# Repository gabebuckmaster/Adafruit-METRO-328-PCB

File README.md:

# Stanford-EE-Metro-Mini

Microchip/Atmel generously donated ATMega328 chips for use in Stanford Electrical Engineering courses. This fork of the Adafruit Metro (Mini) repository contains the design files for our build of the Metro Mini using these donated components.

##*PCB files for the Adafruit METRO 328*

*Format is EagleCAD schematic and board layout*

*For more details, check out the product page at*

  * https://www.adafruit.com/products/2466

*Adafruit invests time and resources providing this open source design, please support Adafruit and open-source hardware by purchasing products from Adafruit!*

*Designed by Adafruit Industries.*

*Creative Commons Attribution, Share-Alike license, check license.txt for more information. Derivative of "Arduino UNO R3 Reference design" (http://www.arduino.cc/en/Main/ArduinoBoardUno)*

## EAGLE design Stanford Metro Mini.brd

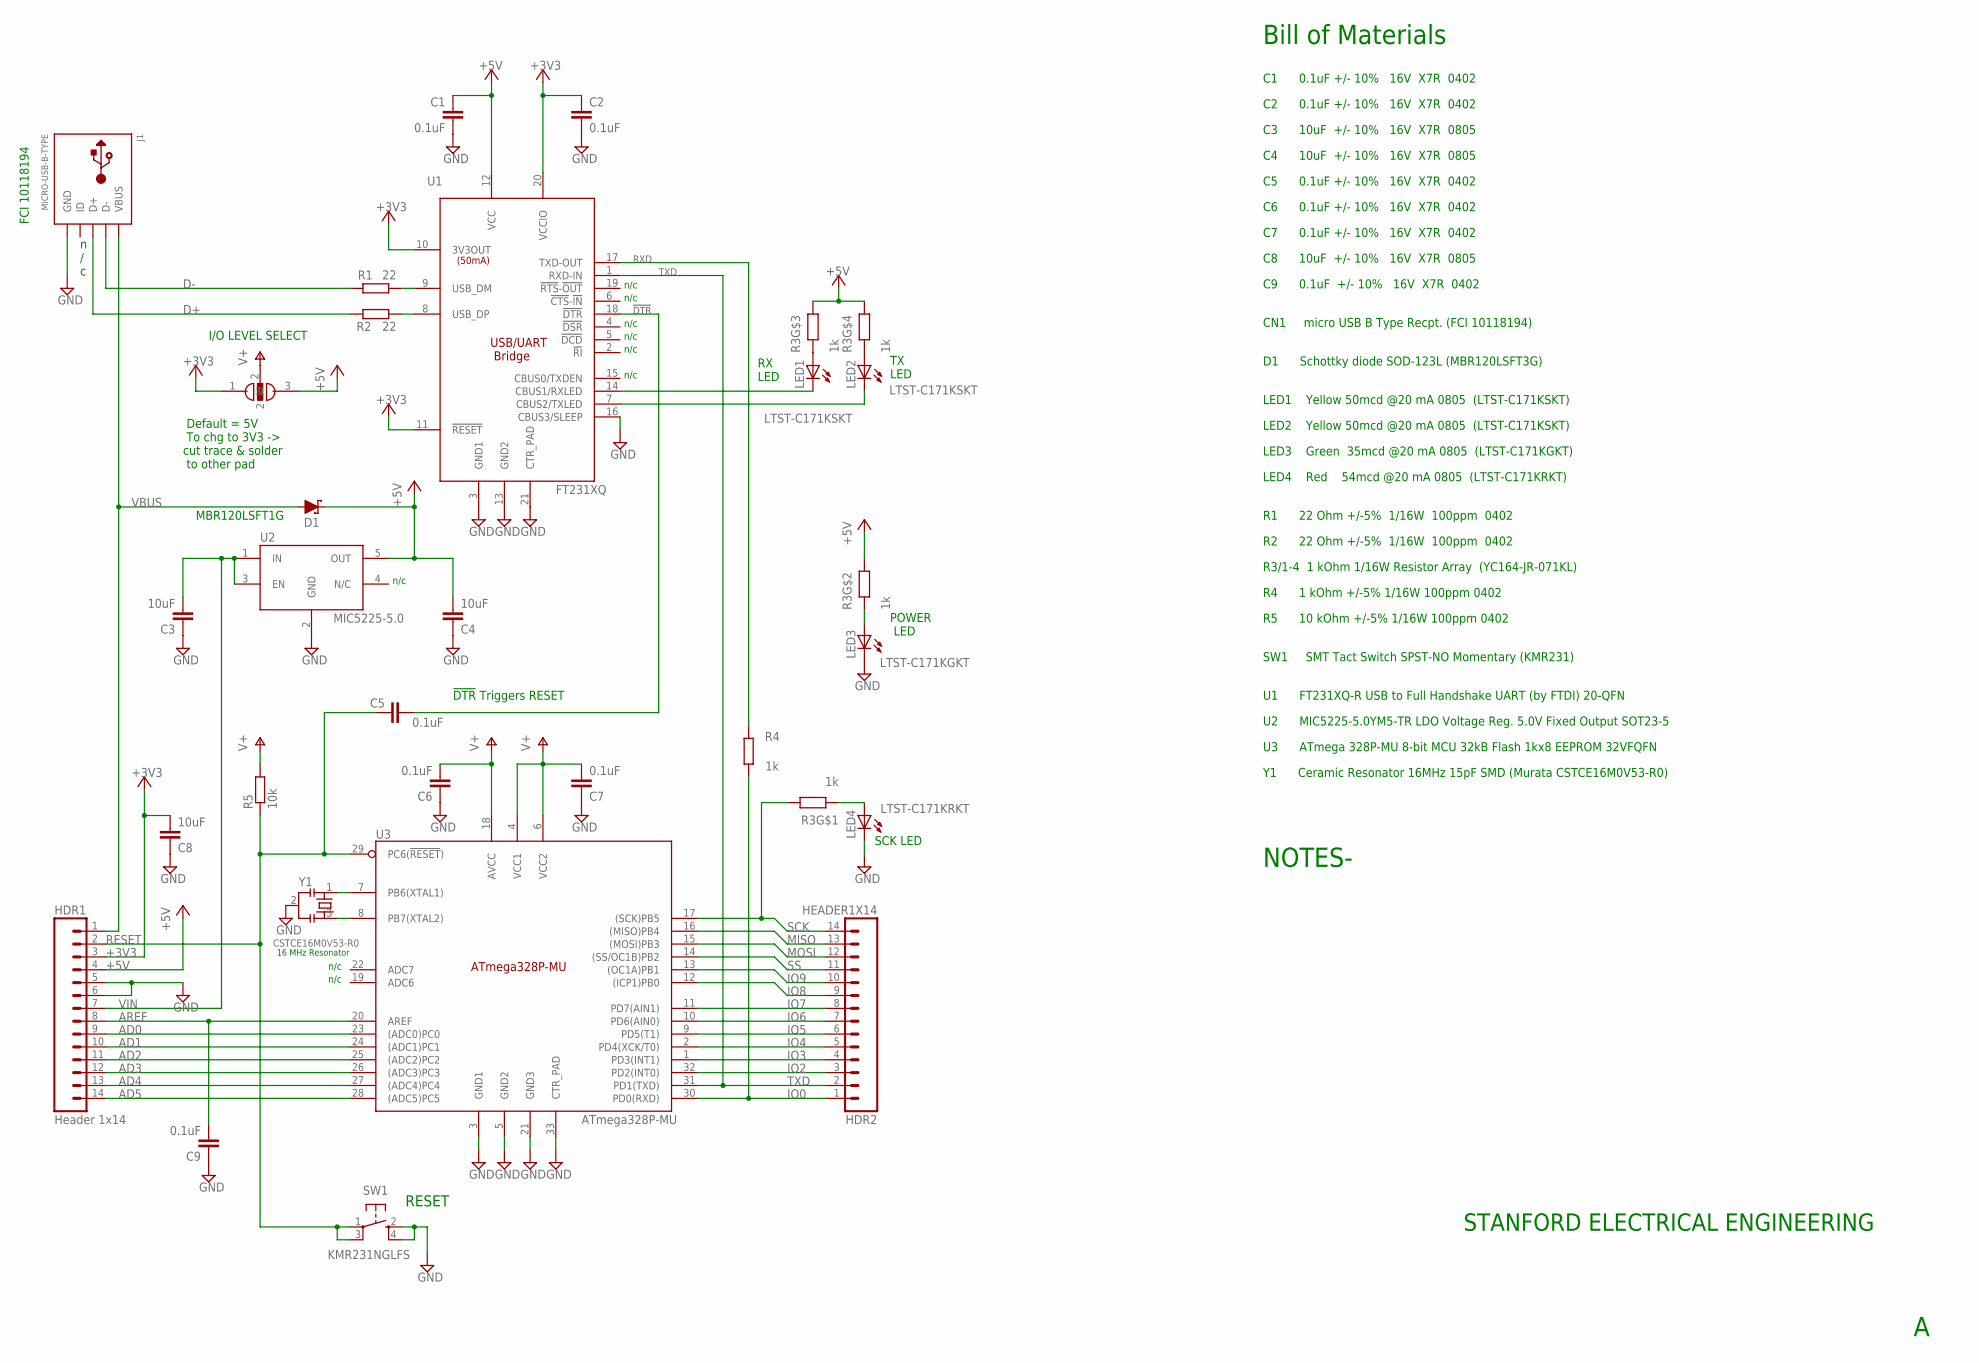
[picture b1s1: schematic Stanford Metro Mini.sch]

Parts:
C1, C2, C5, C6, C7, C9: 0.1uF; C0402
C3, C4, C8: 10uF; C0805
D1: SCHOTTKY; SOD123
HDR1: Header 1x14; 1X14
HDR2: HEADER1X14; 1X14
J1: MICRO-USB-B-TYPE; 10118194-MICRO-USB
LED1, LED2: LTST-C171KSKT; CHIPLED_0805
LED3: LTST-C171KGKT; CHIPLED_0805
LED4: LTST-C171KRKT; CHIPLED_0805
R1, R2: 22; R0402
R3: 1k; R-ARRAY
R4: 1k; R0402
R5: 10k; R0402
SW1: KMR231NGLFS; KMR2
U1: FT231XQ; QFN20
U2: MIC5225-5.0; SOT23-5
U3: ATmega328P-MU; VQFN-32_CTR-PAD
U$1: V_SELECT
Y1: CSTCE16M0V53-R0; CSTCE

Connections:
!DTR: C5.2, U1.18 (!DTR!)
+3V3: C2.1, C8.2, HDR1.3, U1.10 (3V3OUT), U1.11 (!RESET!), U1.20 (VCCIO), U$1.1
+5V: C1.1, C4.2, D1.1 (C), HDR1.4, R3.2B (B), R3.3B (B), R3.4B (B), U1.12 (VCC), U2.5 (OUT), U$1.3
AD0: HDR1.9, U3.23 ((ADC0)PC0)
AD1: HDR1.10, U3.24 ((ADC1)PC1)
AD2: HDR1.11, U3.25 ((ADC2)PC2)
AD3: HDR1.12, U3.26 ((ADC3)PC3)
AD4: HDR1.13, U3.27 ((ADC4)PC4)
AD5: HDR1.14, U3.28 ((ADC5)PC5)
AREF: C9.2, HDR1.8, U3.20 (AREF)
D+: J1.3 (D+), R2.1
D-: J1.2 (D-), R1.1
GND: C1.2, C2.2, C3.1, C4.1, C6.1, C7.1, C8.1, C9.1, HDR1.5, HDR1.6, J1.5 (GND), LED3.C, LED4.C, SW1.2 (S), SW1.4 (S1), U1.3 (GND1), U1.13 (GND2), U1.16 (CBUS3/SLEEP), U1.21 (CTR_PAD), U2.2 (GND), U3.3 (GND1), U3.5 (GND2), U3.21 (GND3), U3.33 (CTR_PAD), Y1.2
IO0: HDR2.1, R4.1, U3.30 (PD0(RXD))
IO2: HDR2.3, U3.32 (PD2(INT0))
IO3: HDR2.4, U3.1 (PD3(INT1))
IO4: HDR2.5, U3.2 (PD4(XCK/T0))
IO5: HDR2.6, U3.9 (PD5(T1))
IO6: HDR2.7, U3.10 (PD6(AIN0))
IO7: HDR2.8, U3.11 (PD7(AIN1))
IO8: HDR2.9, U3.12 ((ICP1)PB0)
IO9: HDR2.10, U3.13 ((OC1A)PB1)
MISO: HDR2.13, U3.16 ((MISO)PB4)
MOSI: HDR2.12, U3.15 ((MOSI)PB3)
unnamed: LED1.A, R3.3A (A)
unnamed: LED3.A, R3.2A (A)
unnamed: R1.2, U1.9 (USB_DM)
unnamed: R2.2, U1.8 (USB_DP)
unnamed: LED2.A, R3.4A (A)
unnamed: LED4.A, R3.1A (A)
unnamed: U3.7 (PB6(XTAL1)), Y1.1
unnamed: U3.8 (PB7(XTAL2)), Y1.3
RESET: C5.1, HDR1.2, R5.1, SW1.1, SW1.3 (P1), U3.29 (PC6(!RESET!))
RXD: R4.2, U1.17 (TXD-OUT)
RX_LED: LED1.C, U1.14 (CBUS1/RXLED)
SCK: HDR2.14, R3.1B (B), U3.17 ((SCK)PB5)
SS: HDR2.11, U3.14 ((SS/OC1B)PB2)
TXD: HDR2.2, U1.1 (RXD-IN), U3.31 (PD1(TXD))
TX_LED: LED2.C, U1.7 (CBUS2/TXLED)
V+: C6.2, C7.2, R5.2, U3.4 (VCC1), U3.6 (VCC2), U3.18 (AVCC), U$1.2
VBUS: D1.2 (A), HDR1.1, J1.1 (VBUS)
VIN: C3.2, HDR1.7, U2.1 (IN), U2.3 (EN)

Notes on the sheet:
!DTR! Triggers RESET
n / c
SCK LED
TX LED
RX LED
POWER LED
16 MHz Resonator
Default = 5V To chg to 3V3 -> cut trace & solder to other pad
I/O LEVEL SELECT
MBR120LSFT1G
n/c
RESET
C1 0.1uF +/- 10% 16V X7R 0402
C2 0.1uF +/- 10% 16V X7R 0402
C3 10uF +/- 10% 16V X7R 0805
C4 10uF +/- 10% 16V X7R 0805
C5 0.1uF +/- 10% 16V X7R 0402
C6 0.1uF +/- 10% 16V X7R 0402
C7 0.1uF +/- 10% 16V X7R 0402
C8 10uF +/- 10% 16V X7R 0805
C9 0.1uF +/- 10% 16V X7R 0402
D1 Schottky diode SOD-123L (MBR120LSFT3G)
LED1 Yellow 50mcd @20 mA 0805 (LTST-C171KSKT)
LED2 Yellow 50mcd @20 mA 0805 (LTST-C171KSKT)
LED3 Green 35mcd @20 mA 0805 (LTST-C171KGKT)
LED4 Red 54mcd @20 mA 0805 (LTST-C171KRKT)
R1 22 Ohm +/-5% 1/16W 100ppm 0402
R3/1-4 1 kOhm 1/16W Resistor Array (YC164-JR-071KL)
R2 22 Ohm +/-5% 1/16W 100ppm 0402
R4 1 kOhm +/-5% 1/16W 100ppm 0402
R5 10 kOhm +/-5% 1/16W 100ppm 0402
CN1 micro USB B Type Recpt. (FCI 10118194)
SW1 SMT Tact Switch SPST-NO Momentary (KMR231)
U1 FT231XQ-R USB to Full Handshake UART (by FTDI) 20-QFN
U2 MIC5225-5.0YM5-TR LDO Voltage Reg. 5.0V Fixed Output SOT23-5
U3 ATmega 328P-MU 8-bit MCU 32kB Flash 1kx8 EEPROM 32VFQFN
Y1 Ceramic Resonator 16MHz 15pF SMD (Murata CSTCE16M0V53-R0)
Bill of Materials
STANFORD ELECTRICAL ENGINEERING
NOTES-

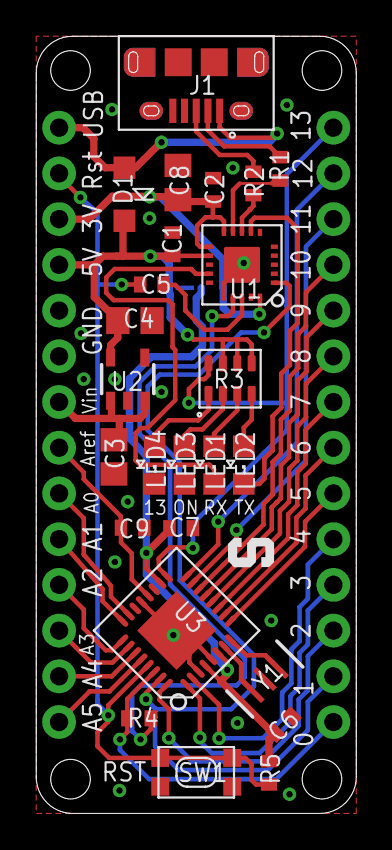
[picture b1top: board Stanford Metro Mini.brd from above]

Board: 2 copper layers, 17.8 x 43.2 mm, 28 parts (1 on the bottom side), 42 nets.

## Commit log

2017-07-26 Initial Commit
    Initial commit of our version of the metro mini.
2017-08-08 Fixed issues with first board run
    Fixed solder paste
    Adjusted QFN pad sizes
    Added the cam file to make regenerating gerbers easier
    Regenerated gerbers
    Generated SVGs of solder paste layer for laser cutting stencils
2017-08-08 Updated component placement guide and regenerated gerbers
    Updated component placement guide and regenerated gerbers
2017-08-08 Added images to README.md
    Added images to README.md
2017-08-08 Brightened pictures of board
    Brightened pictures of board
2019-01-29 Generated pick and place files
    Generated pick and place files
